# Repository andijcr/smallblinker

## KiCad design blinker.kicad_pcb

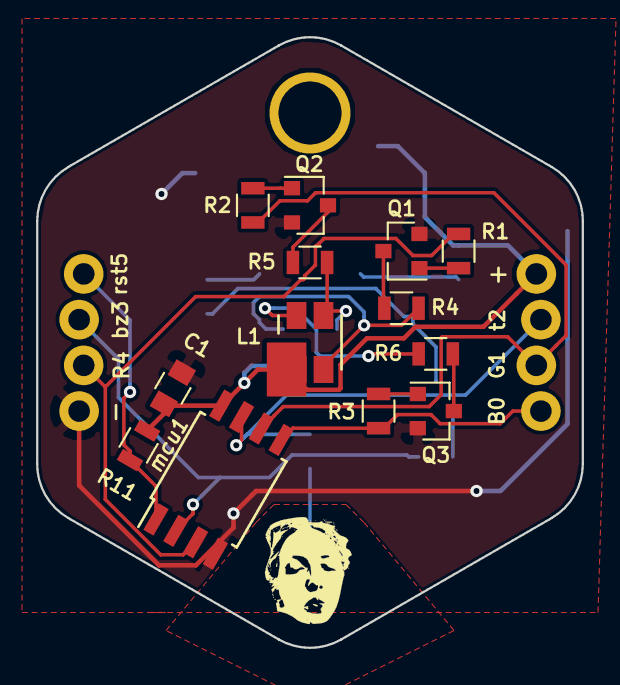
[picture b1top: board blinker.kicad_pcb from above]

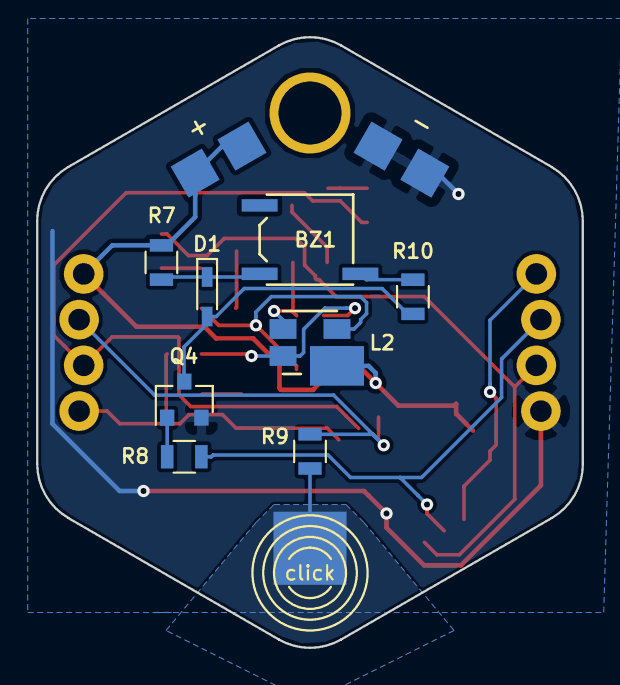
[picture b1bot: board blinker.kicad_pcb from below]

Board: 2 copper layers, 30.3 x 33.9 mm, 32 parts (11 on the bottom side), 22 nets.

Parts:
+: TEST_1P; SolderWirePad_single_1-2mmDrill
+#2: TEST_1P; singlesolderpad
-: TEST_1P; SolderWirePad_single_1-2mmDrill
-#2: TEST_1P; singlesolderpad
B0: TEST_1P; SolderWirePad_single_1-2mmDrill
BZ1: Magnetic Buzzer; t72-0505
C1: 100nf; C_0805
D1: D_Zener; D_SC-80_HandSoldering
G1: TEST_1P; SolderWirePad_single_1-2mmDrill
J9: TOUCH_PAD_COPPER; 1Pin
L1, L2: ASMB-MTB0-0A3A2
Q1, Q2, Q3, Q4: NTR4003NT3G; SOT-23
R1, R2, R3, R8: 82R; R_0805
R4, R5, R6, R10: 33R; R_0805
R4#2: TEST_1P; SolderWirePad_single_1-2mmDrill
R7: 10R; R_0805
R9, R11: 20K; R_0805
bz3: TEST_1P; SolderWirePad_single_1-2mmDrill
mcu1: ATTINY85V-10SU; SOIJ-8_5.3x5.3mm_Pitch1.27mm
rst5: TEST_1P; SolderWirePad_single_1-2mmDrill
t2: TEST_1P; SolderWirePad_single_1-2mmDrill

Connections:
/BLUE: B0.1, R3.2, mcu1.5
/BLUE_MOS: L1.2, L2.2, R6.2
/BUZZER: R8.2, bz3.1, mcu1.2
/GREEN: G1.1, R2.2, mcu1.6
/GREEN_MOS: L1.3, L2.3, R5.2
/RED: R1.2, R4#2.1, mcu1.3
/RED_MOS: L1.4, L2.4, R4.2
/RESET: R11.1, mcu1.1, rst5.1
/TOUCH: R9.1, mcu1.7, t2.1
GND: -.1, -#2.1, C1.2, Q1.2, Q2.2, Q3.2, Q4.2, mcu1.4
unnamed: BZ1.1, D1.1, R7.2
unnamed: BZ1.2, R10.2
unnamed: D1.2, Q4.3, R10.1
unnamed: J9.1, R9.2
unnamed: Q1.1, R1.1
unnamed: Q1.3, R4.1
unnamed: Q2.1, R2.1
unnamed: Q2.3, R5.1
unnamed: Q3.1, R3.1
unnamed: Q3.3, R6.1
unnamed: Q4.1, R8.1
VCC: +.1, +#2.1, C1.1, L1.1, L2.1, R7.1, R11.2, mcu1.8

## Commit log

2017-09-04 init from previous work
2017-09-04 decouplign cap and pullup on reset, plus routing almost done
2017-09-06 pdc not in sync with sch, but silk almost done
2017-09-07 drill and cosmetic
2017-10-29 assembld board, basic funcs tested. now working on version 0.2
2017-11-24 2 version, already built, ready to be tested
